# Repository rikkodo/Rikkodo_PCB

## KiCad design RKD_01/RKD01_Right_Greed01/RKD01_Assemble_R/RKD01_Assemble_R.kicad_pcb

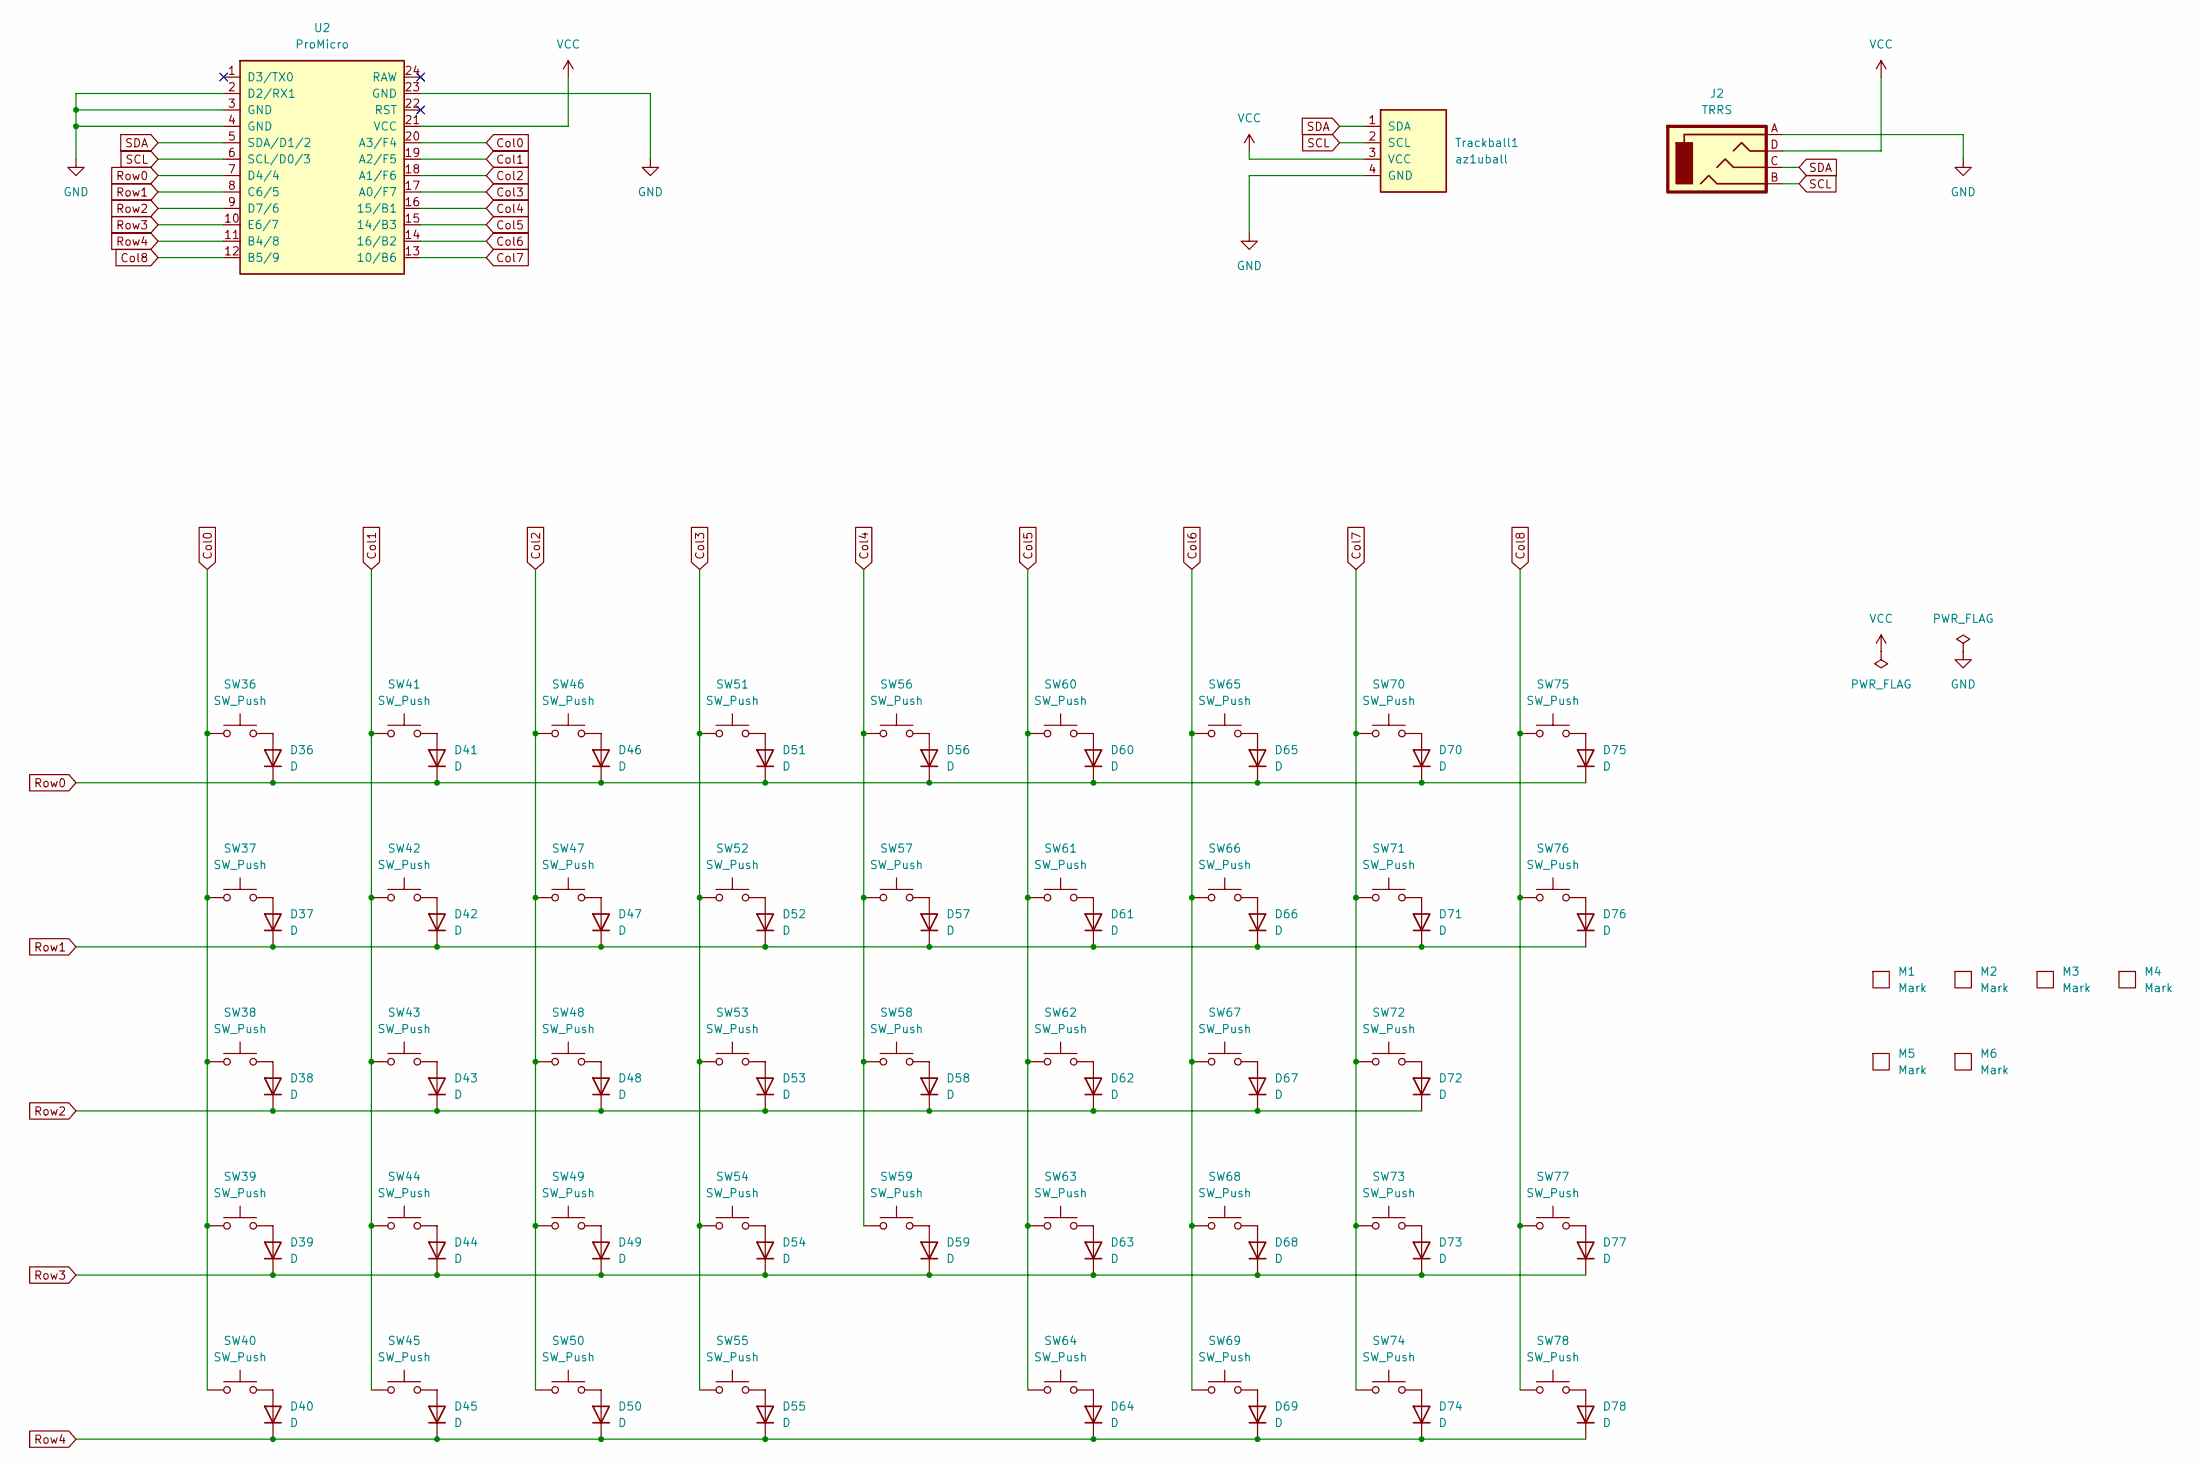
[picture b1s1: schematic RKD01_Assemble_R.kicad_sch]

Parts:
D36, D37, D38, D39, D40, D41, D42, D43, D44, D45, D46, D47, D48, D49, D50, D51, D52, D53, D54, D55, D56, D57, D58, D59, D60, D61, D62, D63, D64, D65, D66, D67, D68, D69, D70, D71, D72, D73, D74, D75, D76, D77, D78: D; Diode_TH_SMD
J2: TRRS; TRRS_PJ-320A
M1, M2, M3, M4: Mark; m2_Spacer_Hole_hex
M5, M6: Mark; m2_Screw_Hole
SW36, SW37, SW38, SW39, SW40, SW41, SW42, SW43, SW44, SW45, SW46, SW47, SW48, SW49, SW50, SW51, SW52, SW53, SW54, SW55, SW56, SW57, SW58, SW59, SW60, SW61, SW62, SW63, SW64, SW65, SW66, SW67, SW68, SW69, SW70, SW71, SW73, SW74, SW76, SW77, SW78: SW_Push; Choc_Hotswap_1u
SW72, SW75: SW_Push; Choc_Hotswap_2u_Stab
Trackball1: az1uball; AZ1UBALL
U2: ProMicro; ProMicro_r

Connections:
Col0: SW36.2, SW37.2, SW38.2, SW39.2, SW40.2, U2.20 (A3/F4)
Col1: SW41.2, SW42.2, SW43.2, SW44.2, SW45.2, U2.19 (A2/F5)
Col2: SW46.2, SW47.2, SW48.2, SW49.2, SW50.2, U2.18 (A1/F6)
Col3: SW51.2, SW52.2, SW53.2, SW54.2, SW55.2, U2.17 (A0/F7)
Col4: SW56.2, SW57.2, SW58.2, SW59.2, U2.16 (15/B1)
Col5: SW60.2, SW61.2, SW62.2, SW63.2, SW64.2, U2.15 (14/B3)
Col6: SW65.2, SW66.2, SW67.2, SW68.2, SW69.2, U2.14 (16/B2)
Col7: SW70.2, SW71.2, SW72.2, SW73.2, SW74.2, U2.13 (10/B6)
Col8: SW75.2, SW76.2, SW77.2, SW78.2, U2.12 (B5/9)
GND: J2.A, Trackball1.4 (GND), U2.2 (D2/RX1), U2.3 (GND), U2.4 (GND), U2.23 (GND)
unnamed: D36.2 (A), SW36.1
unnamed: D37.2 (A), SW37.1
unnamed: D38.2 (A), SW38.1
unnamed: D39.2 (A), SW39.1
unnamed: D40.2 (A), SW40.1
unnamed: D41.2 (A), SW41.1
unnamed: D42.2 (A), SW42.1
unnamed: D43.2 (A), SW43.1
unnamed: D44.2 (A), SW44.1
unnamed: D45.2 (A), SW45.1
unnamed: D46.2 (A), SW46.1
unnamed: D47.2 (A), SW47.1
unnamed: D48.2 (A), SW48.1
unnamed: D49.2 (A), SW49.1
unnamed: D50.2 (A), SW50.1
unnamed: D51.2 (A), SW51.1
unnamed: D52.2 (A), SW52.1
unnamed: D53.2 (A), SW53.1
unnamed: D54.2 (A), SW54.1
unnamed: D55.2 (A), SW55.1
unnamed: D56.2 (A), SW56.1
unnamed: D57.2 (A), SW57.1
unnamed: D58.2 (A), SW58.1
unnamed: D59.2 (A), SW59.1
unnamed: D60.2 (A), SW60.1
unnamed: D61.2 (A), SW61.1
unnamed: D62.2 (A), SW62.1
unnamed: D63.2 (A), SW63.1
unnamed: D64.2 (A), SW64.1
unnamed: D65.2 (A), SW65.1
unnamed: D66.2 (A), SW66.1
unnamed: D67.2 (A), SW67.1
unnamed: D68.2 (A), SW68.1
unnamed: D69.2 (A), SW69.1
unnamed: D70.2 (A), SW70.1
unnamed: D71.2 (A), SW71.1
unnamed: D72.2 (A), SW72.1
unnamed: D73.2 (A), SW73.1
unnamed: D74.2 (A), SW74.1
unnamed: D75.2 (A), SW75.1
unnamed: D76.2 (A), SW76.1
unnamed: D77.2 (A), SW77.1
unnamed: D78.2 (A), SW78.1
Reset: U2.22 (RST)
Row0: D36.1 (K), D41.1 (K), D46.1 (K), D51.1 (K), D56.1 (K), D60.1 (K), D65.1 (K), D70.1 (K), D75.1 (K), U2.7 (D4/4)
Row1: D37.1 (K), D42.1 (K), D47.1 (K), D52.1 (K), D57.1 (K), D61.1 (K), D66.1 (K), D71.1 (K), D76.1 (K), U2.8 (C6/5)
Row2: D38.1 (K), D43.1 (K), D48.1 (K), D53.1 (K), D58.1 (K), D62.1 (K), D67.1 (K), D72.1 (K), U2.9 (D7/6)
Row3: D39.1 (K), D44.1 (K), D49.1 (K), D54.1 (K), D59.1 (K), D63.1 (K), D68.1 (K), D73.1 (K), D77.1 (K), U2.10 (E6/7)
Row4: D40.1 (K), D45.1 (K), D50.1 (K), D55.1 (K), D64.1 (K), D69.1 (K), D74.1 (K), D78.1 (K), U2.11 (B4/8)
SCL: J2.B, Trackball1.2 (SCL), U2.6 (SCL/D0/3)
SDA: J2.C, Trackball1.1 (SDA), U2.5 (SDA/D1/2)
VCC: J2.D, Trackball1.3 (VCC), U2.21 (VCC)

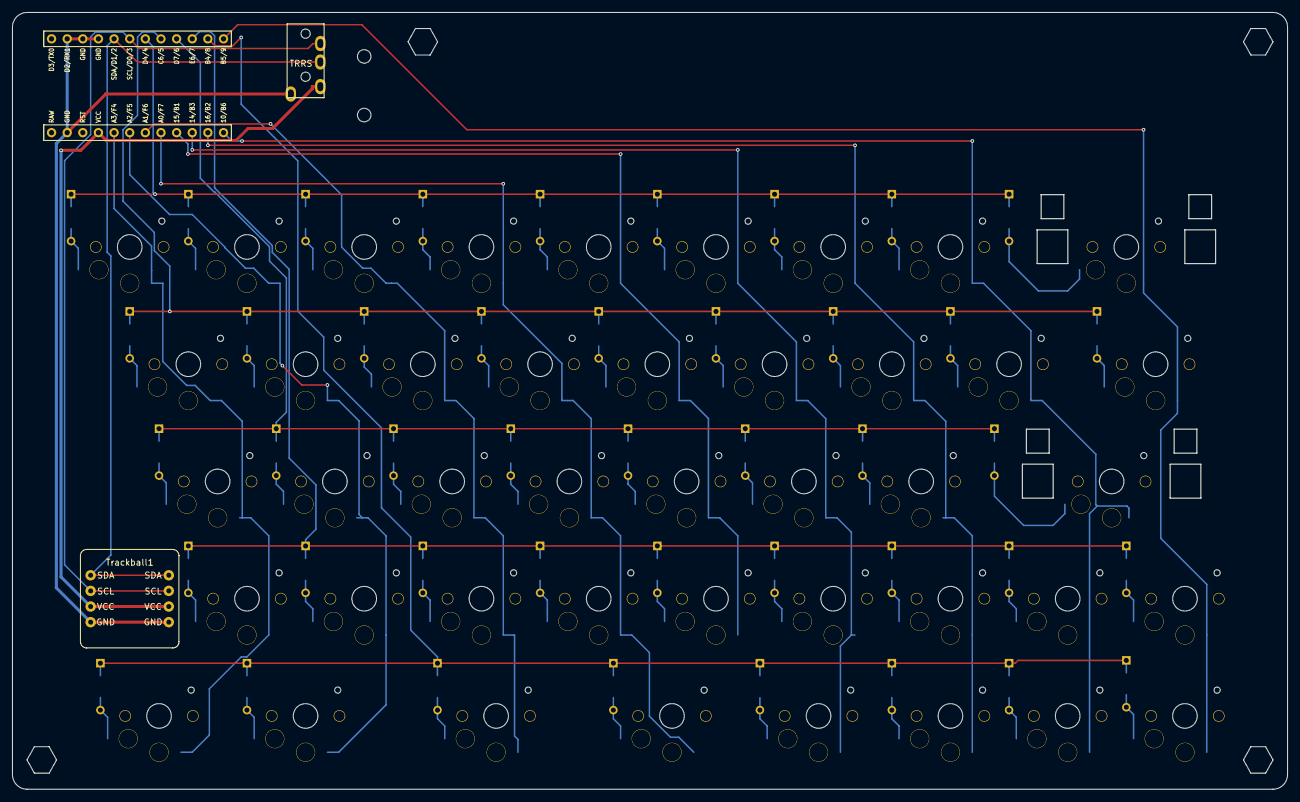
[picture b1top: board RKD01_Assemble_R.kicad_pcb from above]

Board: 2 copper layers, 207.2 x 126.2 mm, 95 parts (0 on the bottom side), 61 nets.
